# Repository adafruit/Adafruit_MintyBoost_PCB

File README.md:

# MintyBoost Kit

<a href="http://www.adafruit.com/products/14"><br/>Click here to purchase one from the Adafruit shop</a>

The world's first and only open-source hardware charger: The MintyBoost®!

__New version!__ Works with the new iPhone 4 & 5 and more! __Please review the [Minty Boost project page(s)](https://learn.adafruit.com/minty-boost) before purchase and assembly!, some phones require different modifications to the kit to charge properly! Some phones such as the iPhone 3gs are very sensitive to charging via USB and may not work in all environments or configurations.__

Make your own iPod/iPhone/GPS/etc... battery-pack and recharger!
This project includes all the electronic parts necessary to build your own MintyBoost: a small & simple (but very powerful) USB charger for your iPod (or other mp3 player), camera, cell phone, and any other gadget you can plug into a USB port to charge.

The charger circuitry and 2 AA batteries fit into an small space such as an Altoids gum or mint tin, and will run your iPod for hours, 2.5x more than you'd get from a 9V USB charger! You can use rechargeable batteries too.

__New In Version 3:__ Provides 500mA @ 5V, tested and designed to work with all the latest iGadgets including the latest iPhones and iPods, etc., improved efficiency for high-drain devices, works much better with LiPoly battery mods.

Kit comes unassembled and is suitable for beginners. Some soldering tools are necessary but even if you've never soldered before it should be pretty easy.

Read more about the project on the [Minty Boost webpage](https://learn.adafruit.com/minty-boost)

Tested works with: iPods, iTouches and iPhones (including the latest 4G), PSP, DS.. Please see a full listing at [Minty Boost compatibility webpage](https://learn.adafruit.com/minty-boost/compat-v3) to see if your device is tested to work before purchasing. iPhone 3gs is the most finicky of the bunch, tinkering may be required.

Batteries and tin not included. [We have nice tins in the shop](https://www.adafruit.com/product/16), or you can also of course make your own case!

Team this up with a [Lithium Ion/Polymer battery](https://www.adafruit.com/category/67) and [our solar-optimized lithium ion battery charger](https://www.adafruit.com/products/390) to make your own Solar Mintyboost!

### License

Adafruit invests time and resources providing this open source design, please support Adafruit and open-source hardware by purchasing products from [Adafruit](https://www.adafruit.com)!

Designed by Limor Fried/Ladyada for Adafruit Industries.

Creative Commons Attribution/Share-Alike, all text above must be included in any redistribution. See license.txt for additional details.

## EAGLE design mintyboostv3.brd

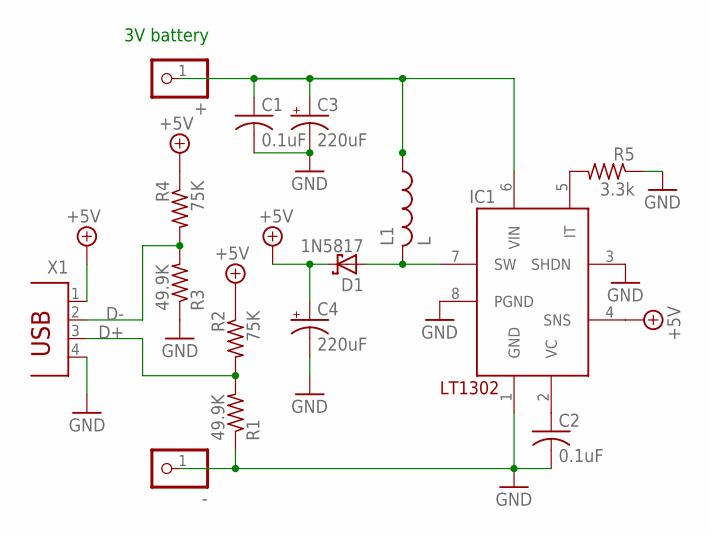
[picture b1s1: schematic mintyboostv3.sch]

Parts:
+: PINHD-1X1; 1X01
-: PINHD-1X1; 1X01
C1, C2: 0.1uF; C025-025X050
C3, C4: 220uF; E2,5-5
D1: 1N5817; DO41-7
IC1: LT1302; DIL08
L1: L; 6000
R1, R3: 49.9K; 0204/5
R2, R4: 75K; 0204/5
R5: 3.3k; 0204/5
X1: PN87520

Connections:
+5V: C4.+, D1.C, IC1.4 (SNS), R2.1, R4.1, X1.1
BATT+: +.1, C1.1, C3.+, IC1.6 (VIN), L1.1
D+: R1.2, R2.2, X1.3
D-: R3.2, R4.2, X1.2
GND: -.1, C1.2, C2.2, C3.-, C4.-, IC1.1 (GND), IC1.3 (SHDN), IC1.8 (PGND), R1.1, R3.1, R5.1, X1.4
unnamed: C2.1, IC1.2 (VC)
unnamed: IC1.5 (IT), R5.2
unnamed: D1.A, IC1.7 (SW), L1.2

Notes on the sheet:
3V battery

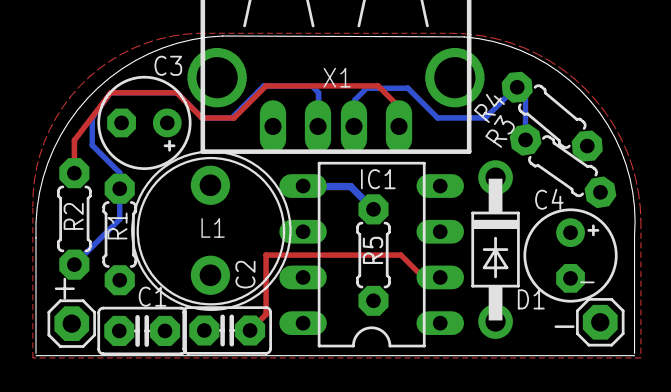
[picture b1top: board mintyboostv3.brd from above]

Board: 2 copper layers, 33.3 x 17.8 mm, 15 parts (0 on the bottom side), 8 nets.

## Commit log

2011-03-05 V3 Eagle files
2011-03-05 V2 files
2019-03-15 readme + image
2019-03-15 added miss
2019-03-15 removed unnecessery files
2026-06-03 update file format to XML
